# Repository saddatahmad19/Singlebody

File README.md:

# Singlebody

A custom mechanical keyboard PCB designed in KiCad 7.

## Overview

Singlebody is an open-source keyboard circuit board project featuring a single-body (non-split) design. This repository contains all the necessary files for manufacturing and assembling the keyboard PCB.

## Repository Contents

- **Singlebody.kicad_pro** - KiCad project file
- **Singlebody.kicad_sch** - Schematic file containing the electrical design
- **Singlebody.kicad_pcb** - PCB layout file with component placement and routing
- **production/** - Manufacturing files (Gerbers, drill files, etc.) ready for PCB fabrication
- **Singlebody-backups/** - Automatic KiCad backup files

## Design Software

This project was created using **KiCad 7**. To view or modify the design files, you'll need:
- [KiCad 7](https://www.kicad.org/download/) or later

## Manufacturing

Production files for PCB fabrication are located in the `production/Singlebody_2024-02-24_15-04-56/` directory. These files can be sent directly to PCB manufacturers such as:
- JLCPCB
- PCBWay
- OSH Park
- Other PCB fabrication services

## Getting Started

1. Clone this repository
2. Open `Singlebody.kicad_pro` in KiCad 7
3. Review the schematic (`Singlebody.kicad_sch`) and PCB layout (`Singlebody.kicad_pcb`)
4. Export

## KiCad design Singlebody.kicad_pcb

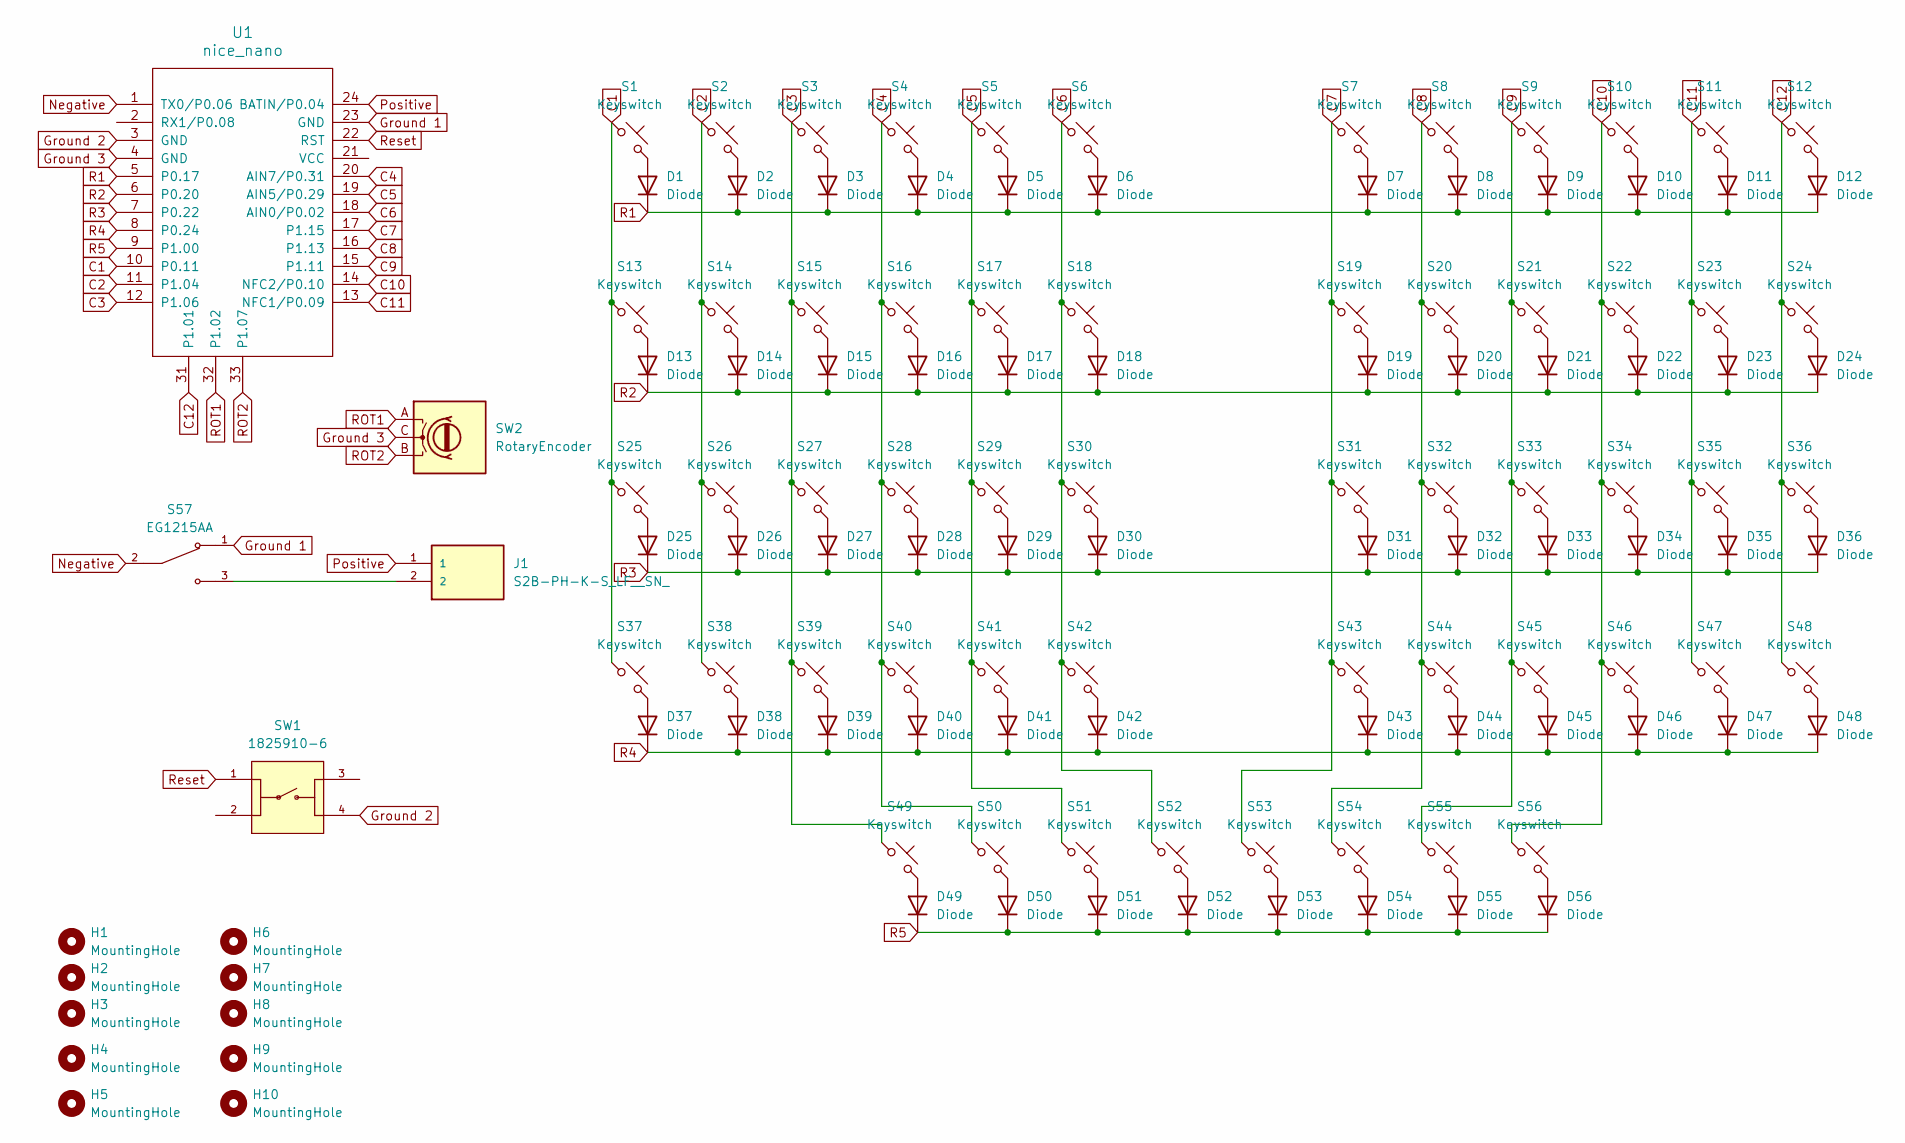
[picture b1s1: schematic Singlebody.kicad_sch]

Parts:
D1, D2, D3, D4, D5, D6, D7, D8, D9, D10, D11, D12, D13, D14, D15, D16, D17, D18, D19, D20, D21, D22, D23, D24, D25, D26, D27, D28, D29, D30, D31, D32, D33, D34, D35, D36, D37, D38, D39, D40, D41, D42, D43, D44, D45, D46, D47, D48, D49, D50, D51, D52, D53, D54, D55, D56: Diode; Diode_SOD-123
H1, H2, H3, H4, H5, H6, H7, H8, H9, H10: MountingHole; MountingHole_2.2mm_M2
J1: S2B-PH-K-S_LF__SN_; JST_S2B-PH-K-S_LF__SN_
S1, S2, S3, S4, S5, S6, S7, S8, S9, S10, S11, S12, S13, S14, S15, S16, S17, S18, S19, S20, S21, S22, S23, S24, S25, S26, S27, S28, S29, S30, S31, S32, S33, S34, S35, S36, S37, S38, S39, S40, S41, S42, S43, S44, S45, S46, S47, S48, S49, S50, S55, S56: Keyswitch; Hotswap_MX_1.00u
S51, S54: Keyswitch; Hotswap_MX_1.50u
S52, S53: Keyswitch; Hotswap_MX_1.50u_90deg
S57: EG1215AA; SW_EG1215AA; PARTREV A
SW1: 1825910-6; SW_1825910-6-4; PARTREV C10
SW2: RotaryEncoder; RotaryEncoder_Alps_EC11E-Switch_Vertical_H20mm
U1: nice_nano

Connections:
C1: S1.1, S13.1, S25.1, S37.1, U1.10 (P0.11)
C2: S2.1, S14.1, S26.1, S38.1, U1.11 (P1.04)
C3: S3.1, S15.1, S27.1, S39.1, S49.1, U1.12 (P1.06)
C4: S4.1, S16.1, S28.1, S40.1, S50.1, U1.20 (AIN7/P0.31)
C5: S5.1, S17.1, S29.1, S41.1, S51.1, U1.19 (AIN5/P0.29)
C6: S6.1, S18.1, S30.1, S42.1, S52.1, U1.18 (AIN0/P0.02)
C7: S7.1, S19.1, S31.1, S43.1, S53.1, U1.17 (P1.15)
C8: S8.1, S20.1, S32.1, S44.1, S54.1, U1.16 (P1.13)
C9: S9.1, S21.1, S33.1, S45.1, S55.1, U1.15 (P1.11)
C10: S10.1, S22.1, S34.1, S46.1, S56.1, U1.14 (NFC2/P0.10)
C11: S11.1, S23.1, S35.1, S47.1, U1.13 (NFC1/P0.09)
C12: S12.1, S24.1, S36.1, S48.1, U1.31 (P1.01)
Ground 1: S57.1, U1.23 (GND)
Ground 2: SW1.4, U1.3 (GND)
Ground 3: SW2.C, U1.4 (GND)
Negative: S57.2, U1.1 (TX0/P0.06)
unnamed: D1.2 (A), S1.2
unnamed: D2.2 (A), S2.2
unnamed: D3.2 (A), S3.2
unnamed: D4.2 (A), S4.2
unnamed: D5.2 (A), S5.2
unnamed: D6.2 (A), S6.2
unnamed: D7.2 (A), S7.2
unnamed: D8.2 (A), S8.2
unnamed: D9.2 (A), S9.2
unnamed: D10.2 (A), S10.2
unnamed: D11.2 (A), S11.2
unnamed: D12.2 (A), S12.2
unnamed: D13.2 (A), S13.2
unnamed: D14.2 (A), S14.2
unnamed: D15.2 (A), S15.2
unnamed: D16.2 (A), S16.2
unnamed: D17.2 (A), S17.2
unnamed: D18.2 (A), S18.2
unnamed: D19.2 (A), S19.2
unnamed: D20.2 (A), S20.2
unnamed: D21.2 (A), S21.2
unnamed: D22.2 (A), S22.2
unnamed: D23.2 (A), S23.2
unnamed: D24.2 (A), S24.2
unnamed: D25.2 (A), S25.2
unnamed: D26.2 (A), S26.2
unnamed: D27.2 (A), S27.2
unnamed: D28.2 (A), S28.2
unnamed: D29.2 (A), S29.2
unnamed: D30.2 (A), S30.2
unnamed: D31.2 (A), S31.2
unnamed: D32.2 (A), S32.2
unnamed: D33.2 (A), S33.2
unnamed: D34.2 (A), S34.2
unnamed: D35.2 (A), S35.2
unnamed: D36.2 (A), S36.2
unnamed: D37.2 (A), S37.2
unnamed: D38.2 (A), S38.2
unnamed: D39.2 (A), S39.2
unnamed: D40.2 (A), S40.2
unnamed: D41.2 (A), S41.2
unnamed: D42.2 (A), S42.2
unnamed: D43.2 (A), S43.2
unnamed: D44.2 (A), S44.2
unnamed: D45.2 (A), S45.2
unnamed: D46.2 (A), S46.2
unnamed: D47.2 (A), S47.2
unnamed: D48.2 (A), S48.2
unnamed: D49.2 (A), S49.2
unnamed: D50.2 (A), S50.2
unnamed: D51.2 (A), S51.2
unnamed: D52.2 (A), S52.2
unnamed: D53.2 (A), S53.2
unnamed: D54.2 (A), S54.2
unnamed: D55.2 (A), S55.2
unnamed: D56.2 (A), S56.2
unnamed: J1.2, S57.3
Positive: J1.1, U1.24 (BATIN/P0.04)
R1: D1.1 (K), D2.1 (K), D3.1 (K), D4.1 (K), D5.1 (K), D6.1 (K), D7.1 (K), D8.1 (K), D9.1 (K), D10.1 (K), D11.1 (K), D12.1 (K), U1.5 (P0.17)
R2: D13.1 (K), D14.1 (K), D15.1 (K), D16.1 (K), D17.1 (K), D18.1 (K), D19.1 (K), D20.1 (K), D21.1 (K), D22.1 (K), D23.1 (K), D24.1 (K), U1.6 (P0.20)
R3: D25.1 (K), D26.1 (K), D27.1 (K), D28.1 (K), D29.1 (K), D30.1 (K), D31.1 (K), D32.1 (K), D33.1 (K), D34.1 (K), D35.1 (K), D36.1 (K), U1.7 (P0.22)
R4: D37.1 (K), D38.1 (K), D39.1 (K), D40.1 (K), D41.1 (K), D42.1 (K), D43.1 (K), D44.1 (K), D45.1 (K), D46.1 (K), D47.1 (K), D48.1 (K), U1.8 (P0.24)
R5: D49.1 (K), D50.1 (K), D51.1 (K), D52.1 (K), D53.1 (K), D54.1 (K), D55.1 (K), D56.1 (K), U1.9 (P1.00)
ROT1: SW2.A, U1.32 (P1.02)
ROT2: SW2.B, U1.33 (P1.07)
Reset: SW1.1, U1.22 (RST)

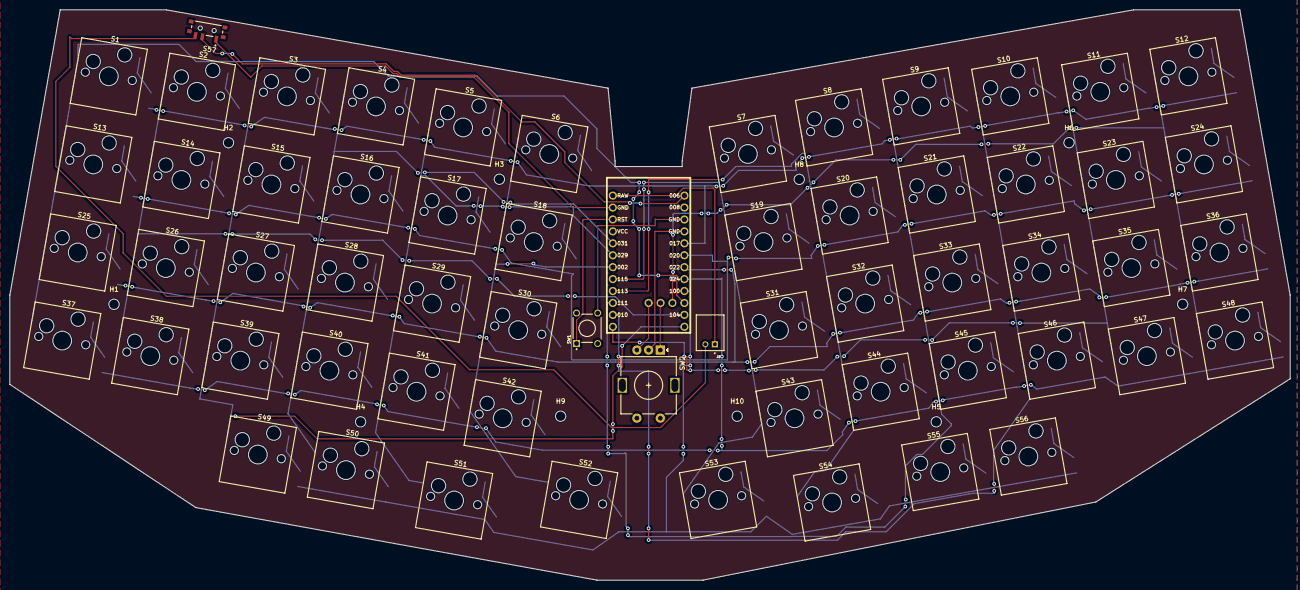
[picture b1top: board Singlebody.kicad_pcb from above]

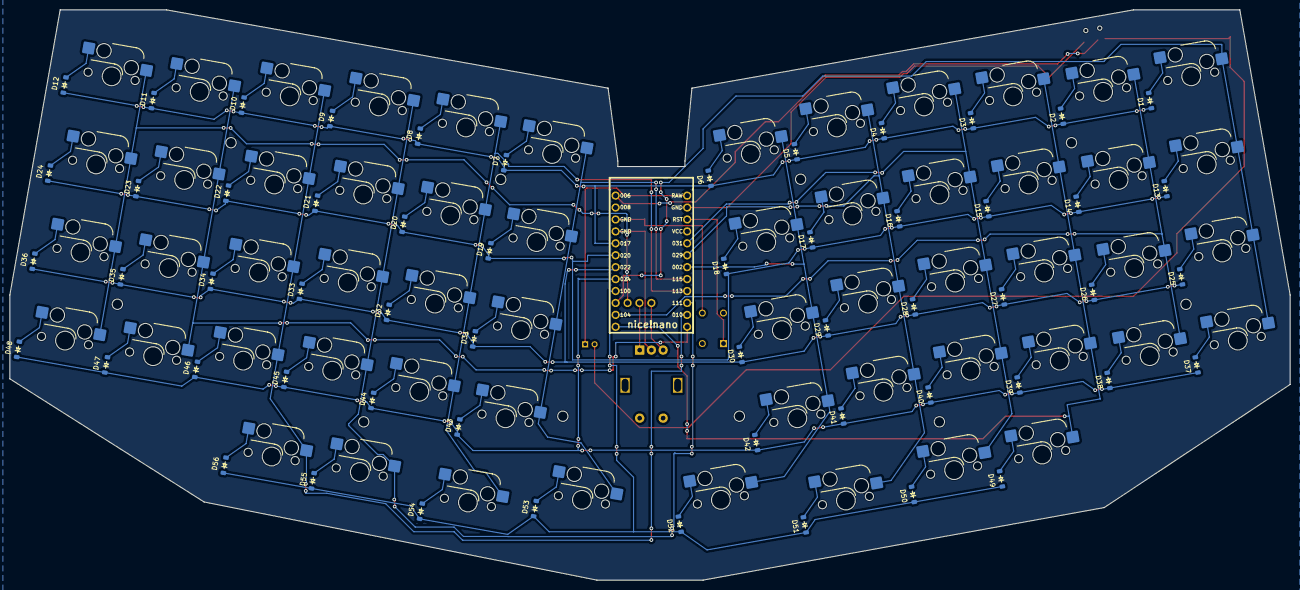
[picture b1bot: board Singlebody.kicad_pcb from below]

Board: 2 copper layers, 272.7 x 121.4 mm, 127 parts (57 on the bottom side), 82 nets.

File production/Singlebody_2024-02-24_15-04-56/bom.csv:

Designator,Footprint,Quantity,Value,LCSC Part #
"D1, D10, D11, D12, D13, D14, D15, D16, D17, D18, D19, D2, D20, D21, D22, D23, D24, D25, D26, D27, D28, D29, D3, D30, D31, D32, D33, D34, D35, D36, D37, D38, D39, D4, D40, D41, D42, D43, D44, D45, D46, D47, D48, D49, D5, D50, D51, D52, D53, D54, D55, D56, D6, D7, D8, D9",Diode_SOD-123,56,Diode,
"H1, H10, H2, H3, H4, H5, H6, H7, H8, H9",MountingHole_2.2mm_M2,10,MountingHole,
J1,JST_S2B-PH-K-S_LF__SN_,1,S2B-PH-K-S_LF__SN_,
"S1, S10, S11, S12, S13, S14, S15, S16, S17, S18, S19, S2, S20, S21, S22, S23, S24, S25, S26, S27, S28, S29, S3, S30, S31, S32, S33, S34, S35, S36, S37, S38, S39, S4, S40, S41, S42, S43, S44, S45, S46, S47, S48, S49, S5, S50, S55, S56, S6, S7, S8, S9",Hotswap_MX_1.00u,52,Keyswitch,
"S51, S54",Hotswap_MX_1.50u,2,Keyswitch,
"S52, S53",Hotswap_MX_1.50u_90deg,2,Keyswitch,
S57,SW_EG1215AA,1,EG1215AA,
SW1,SW_1825910-6-4,1,1825910-6,
SW2,RotaryEncoder_Alps_EC11E-Switch_Vertical_H20mm,1,RotaryEncoder,
U1,nice_nano,1,nice_nano,

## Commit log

2025-10-24 Add README for Singlebody keyboard PCB project
    This README provides an overview of the Singlebody keyboard PCB project, including its contents, design software requirements, manufacturing details, and getting started instructions.
